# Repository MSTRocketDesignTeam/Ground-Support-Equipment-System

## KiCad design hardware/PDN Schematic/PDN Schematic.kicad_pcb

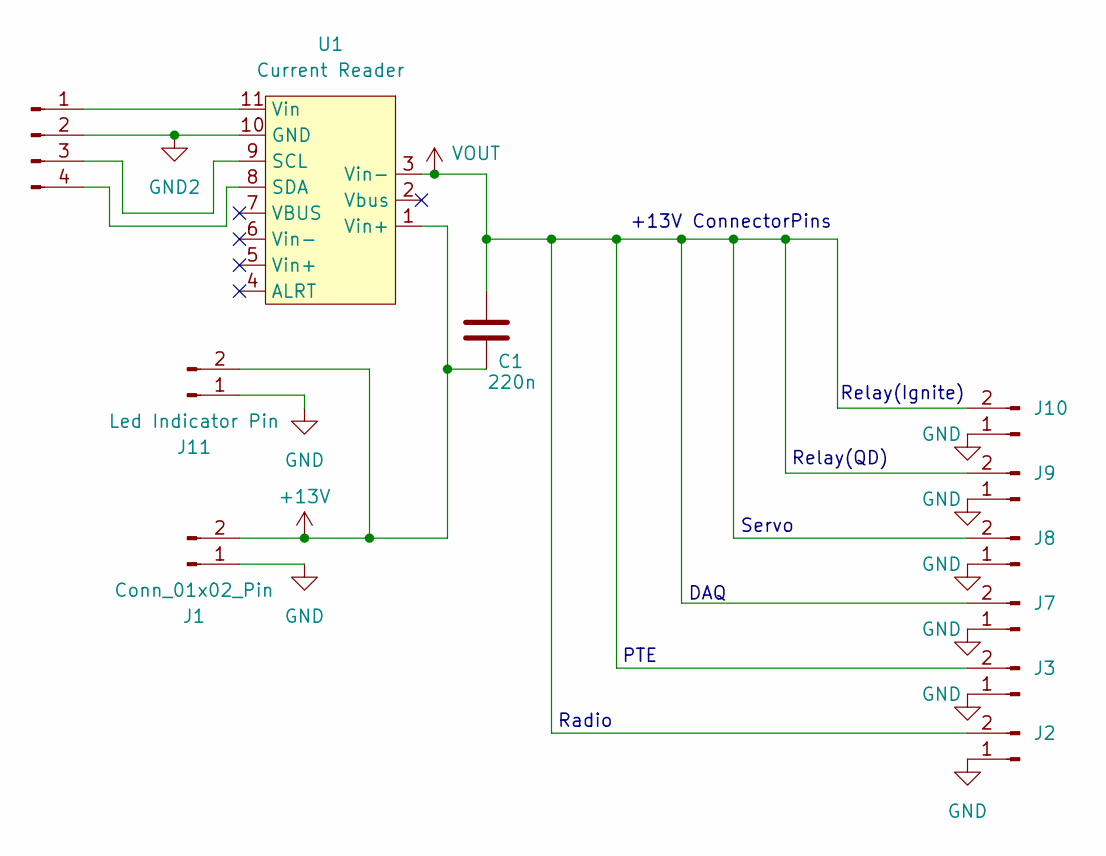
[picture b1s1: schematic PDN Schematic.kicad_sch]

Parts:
C1: 220n; C_0805_2012Metric; DigiKey Digikey: https://www.digikey.com/en/pro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
J1: Conn_01x02_Pin; AMASS_XT60-M_1x02_P7.20mm_Vertical
J2, J3, J7, J8, J9, J10: Conn_01x02_Pin; AMASS_XT30U-M_1x02_P5.0mm_Vertical
J4: Conn_01x04_Pin; PinHeader_1x04_P2.54mm_Vertical
J11: Led Indicator Pin; AMASS_XT30U-M_1x02_P5.0mm_Vertical
U1: Current Reader; INA238_MODULE

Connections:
+13V: C1.2, J1.2, J11.2, U1.1 (Vin+)
GND: J1.1, J2.1, J3.1, J7.1, J8.1, J9.1, J10.1, J11.1
GND2: J4.2, U1.10 (GND)
unnamed: J4.1, U1.11 (Vin)
unnamed: J4.3, U1.9 (SCL)
unnamed: J4.4, U1.8 (SDA)
VOUT: C1.1, J2.2, J3.2, J7.2, J8.2, J9.2, J10.2, U1.3 (Vin-)

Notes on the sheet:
Relay(Ignite)
Servo
Radio
Relay(QD)
+13V ConnectorPins
DAQ
PTE

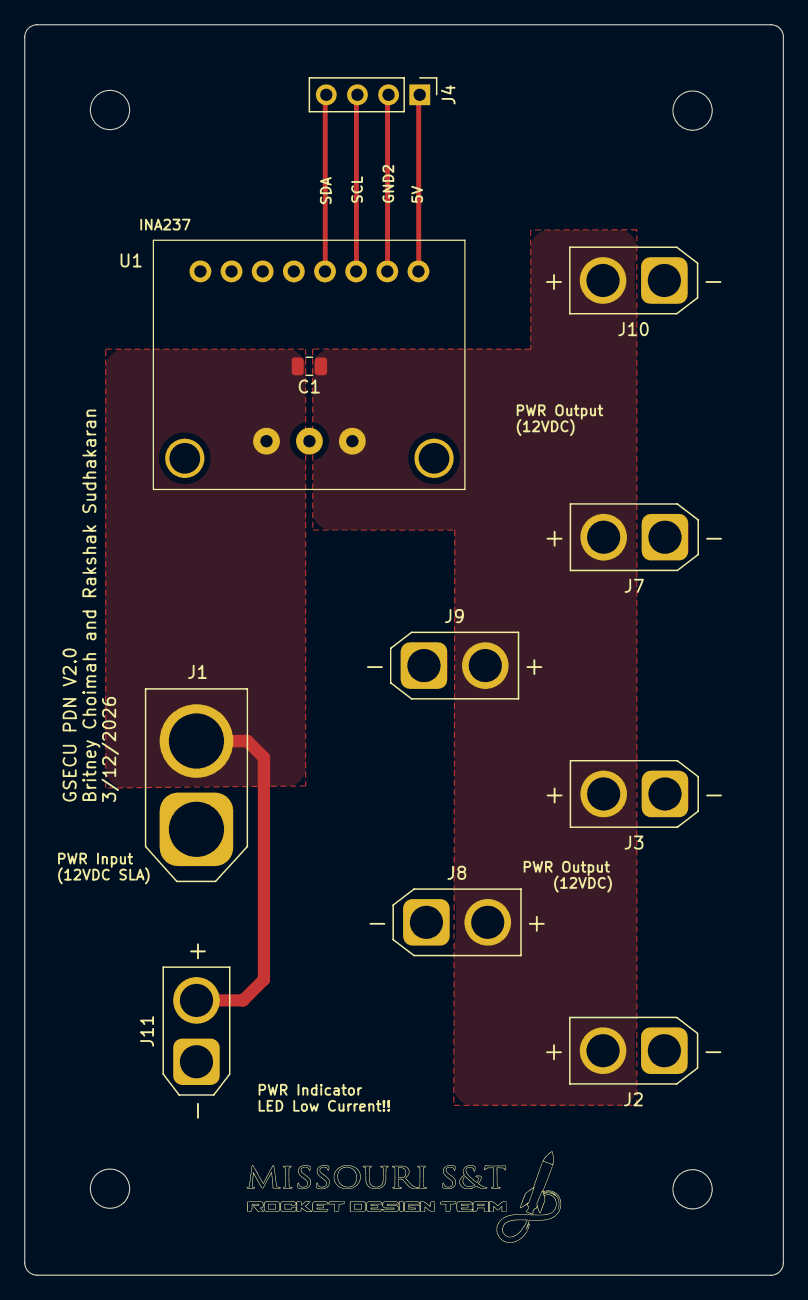
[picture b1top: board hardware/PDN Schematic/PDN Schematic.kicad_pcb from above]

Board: 2 copper layers, 61.9 x 102.0 mm, 11 parts (0 on the bottom side), 7 nets.

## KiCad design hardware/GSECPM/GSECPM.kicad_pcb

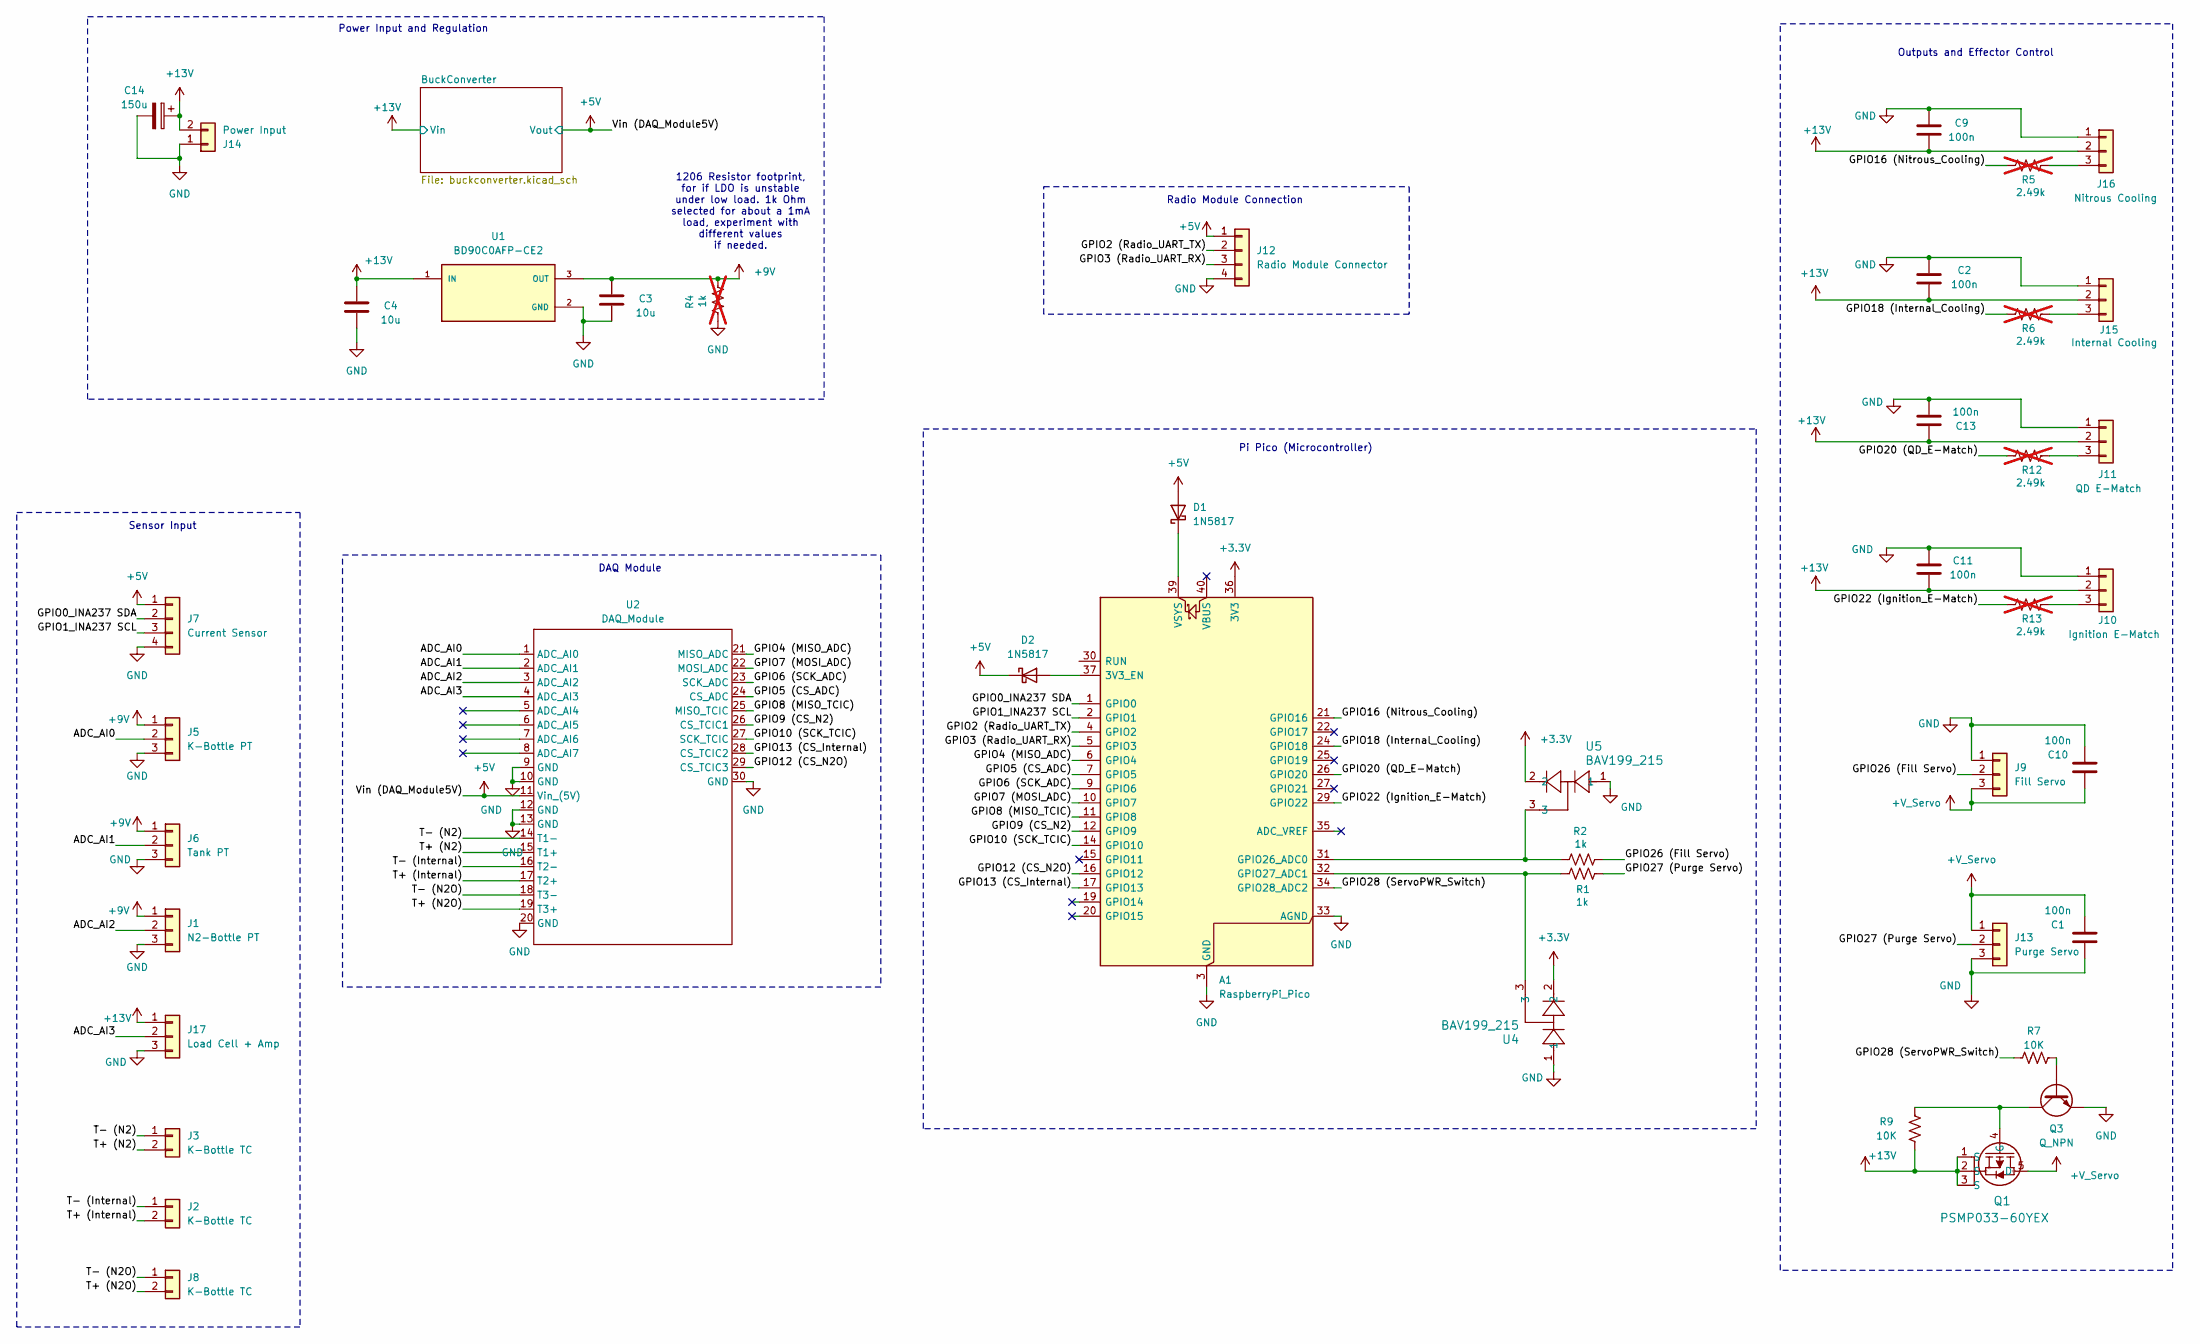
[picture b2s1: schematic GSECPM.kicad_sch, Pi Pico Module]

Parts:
A1: RaspberryPi_Pico; RaspberryPi_Pico_Common_Unspecified
C1, C2, C9, C10, C11, C13: 100n; C_0603_1608Metric
C3, C4: 10u; C_1210_3225Metric
C14: 150u; CAPPRD500W60D1000H1600
D1, D2: 1N5817; D_DO-41_SOD81_P10.16mm_Horizontal
J1: N2-Bottle PT; TerminalBlock_Xinya_XY308-2.54-3P_1x03_P2.54mm_Horizontal
J2, J3, J8: K-Bottle TC; TerminalBlock_Xinya_XY308-2.54-2P_1x02_P2.54mm_Horizontal
J5: K-Bottle PT; TerminalBlock_Xinya_XY308-2.54-3P_1x03_P2.54mm_Horizontal
J6: Tank PT; TerminalBlock_Xinya_XY308-2.54-3P_1x03_P2.54mm_Horizontal
J7: Current Sensor; PinHeader_1x04_P2.54mm_Vertical
J9: Fill Servo; TerminalBlock_Xinya_XY308-2.54-3P_1x03_P2.54mm_Horizontal
J10: Ignition E-Match; PinHeader_1x03_P2.54mm_Vertical
J11: QD E-Match; PinHeader_1x03_P2.54mm_Vertical
J12: Radio Module Connector; PinHeader_1x04_P2.54mm_Vertical
J13: Purge Servo; TerminalBlock_Xinya_XY308-2.54-3P_1x03_P2.54mm_Horizontal
J14: Power Input; AMASS_XT30U-M_1x02_P5.0mm_Vertical
J15: Internal Cooling; PinHeader_1x03_P2.54mm_Vertical
J16: Nitrous Cooling; PinHeader_1x03_P2.54mm_Vertical
J17: Load Cell + Amp; TerminalBlock_Xinya_XY308-2.54-3P_1x03_P2.54mm_Horizontal
Q1: PSMP033-60YEX; LFPAK_SOT669_NEX
Q3: Q_NPN; SOT-323_SC-70
R1, R2: 1k; R_0603_1608Metric
R4: 1k; R_1206_3216Metric; not fitted
R5, R6, R12, R13: 2.49k; R_0603_1608Metric; not fitted
R7, R9: 10K; R_0603_1608Metric
U1: BD90C0AFP-CE2; TO-252-2; PARTREV 23
U2: DAQ_Module
U4, U5: BAV199_215; TO-236AB_NEX

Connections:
+3.3V: A1.36 (3V3), U4.2, U5.2
+5V: D1.2 (A), D2.1 (K), J7.1, J12.1, U2.11 (Vin_(5V)); also elsewhere on the board
+9V: C3.2, J1.1, J5.1, J6.1, R4.1, U1.3 (OUT)
+13V: C2.1, C4.2, C9.1, C11.1, C13.1, C14.1, J10.2, J11.2, J14.2, J15.2, J16.2, J17.1, Q1.1 (S), Q1.2 (S), Q1.3 (S), R9.1, U1.1 (IN); also elsewhere on the board
+V_Servo: C1.2, C10.1, J9.3, J13.1, Q1.5 (D)
/ADC_AI0: J5.2, U2.1 (ADC_AI0)
/ADC_AI1: J6.2, U2.2 (ADC_AI1)
/ADC_AI2: J1.2, U2.3 (ADC_AI2)
/ADC_AI3: J17.2, U2.4 (ADC_AI3)
/GPIO0_INA237 SDA: A1.1 (GPIO0), J7.2
/GPIO1_INA237 SCL: A1.2 (GPIO1), J7.3
/GPIO2 (Radio_UART_TX): A1.4 (GPIO2), J12.2
/GPIO3 (Radio_UART_RX): A1.5 (GPIO3), J12.3
/GPIO4 (MISO_ADC): A1.6 (GPIO4), U2.21 (MISO_ADC)
/GPIO5 (CS_ADC): A1.7 (GPIO5), U2.24 (CS_ADC)
/GPIO6 (SCK_ADC): A1.9 (GPIO6), U2.23 (SCK_ADC)
/GPIO7 (MOSI_ADC): A1.10 (GPIO7), U2.22 (MOSI_ADC)
/GPIO8 (MISO_TCIC): A1.11 (GPIO8), U2.25 (MISO_TCIC)
/GPIO9 (CS_N2): A1.12 (GPIO9), U2.26 (CS_TCIC1)
/GPIO10 (SCK_TCIC): A1.14 (GPIO10), U2.27 (SCK_TCIC)
/GPIO12 (CS_N2O): A1.16 (GPIO12), U2.29 (CS_TCIC3)
/GPIO13 (CS_Internal): A1.17 (GPIO13), U2.28 (CS_TCIC2)
/GPIO16 (Nitrous_Cooling): A1.21 (GPIO16), R5.1
/GPIO18 (Internal_Cooling): A1.24 (GPIO18), R6.1
/GPIO20 (QD_E-Match): A1.26 (GPIO20), R12.1
/GPIO22 (Ignition_E-Match): A1.29 (GPIO22), R13.1
/GPIO26 (Fill Servo): J9.2, R2.1
/GPIO27 (Purge Servo): J13.2, R1.1
/GPIO28 (ServoPWR_Switch): A1.34 (GPIO28_ADC2), R7.2
/T+ (Internal): J2.2, U2.17 (T2+)
/T+ (N2): J3.2, U2.15 (T1+)
/T+ (N2O): J8.2, U2.19 (T3+)
/T- (Internal): J2.1, U2.16 (T2-)
/T- (N2): J3.1, U2.14 (T1-)
/T- (N2O): J8.1, U2.18 (T3-)
GND: A1.3 (GND), A1.8 (GND), A1.13 (GND), A1.18 (GND), A1.23 (GND), A1.28 (GND), A1.33 (AGND), A1.38 (GND), C1.1, C2.2, C3.1, C4.1, C9.2, C10.2, C11.2, C13.2, C14.2, J1.3, J5.3, J6.3, J7.4, J9.1, J10.1, J11.1, J12.4, J13.3, J14.1, J15.1, J16.1, J17.3, Q3.2 (E), R4.2, U1.2 (GND), U2.9 (GND), U2.10 (GND), U2.12 (GND), U2.13 (GND), U2.20 (GND), U2.30 (GND), U4.1, U5.1; also elsewhere on the board
unnamed: A1.37 (3V3_EN), D2.2 (A)
unnamed: A1.31 (GPIO26_ADC0), R2.2, U5.3
unnamed: A1.32 (GPIO27_ADC1), R1.2, U4.3
unnamed: A1.39 (VSYS), D1.1 (K)
unnamed: J10.3, R13.2
unnamed: J11.3, R12.2
unnamed: J15.3, R6.2
unnamed: J16.3, R5.2
unnamed: Q1.4 (G), Q3.3 (C), R9.2
unnamed: Q3.1 (B), R7.1

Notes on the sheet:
1206 Resistor footprint, for if LDO is unstable under low load. 1k Ohm selected for about a 1mA load, experiment with different values if needed.
Power Input and Regulation
Pi Pico (Microcontroller)
Sensor Input
DAQ Module
Outputs and Effector Control
Radio Module Connection

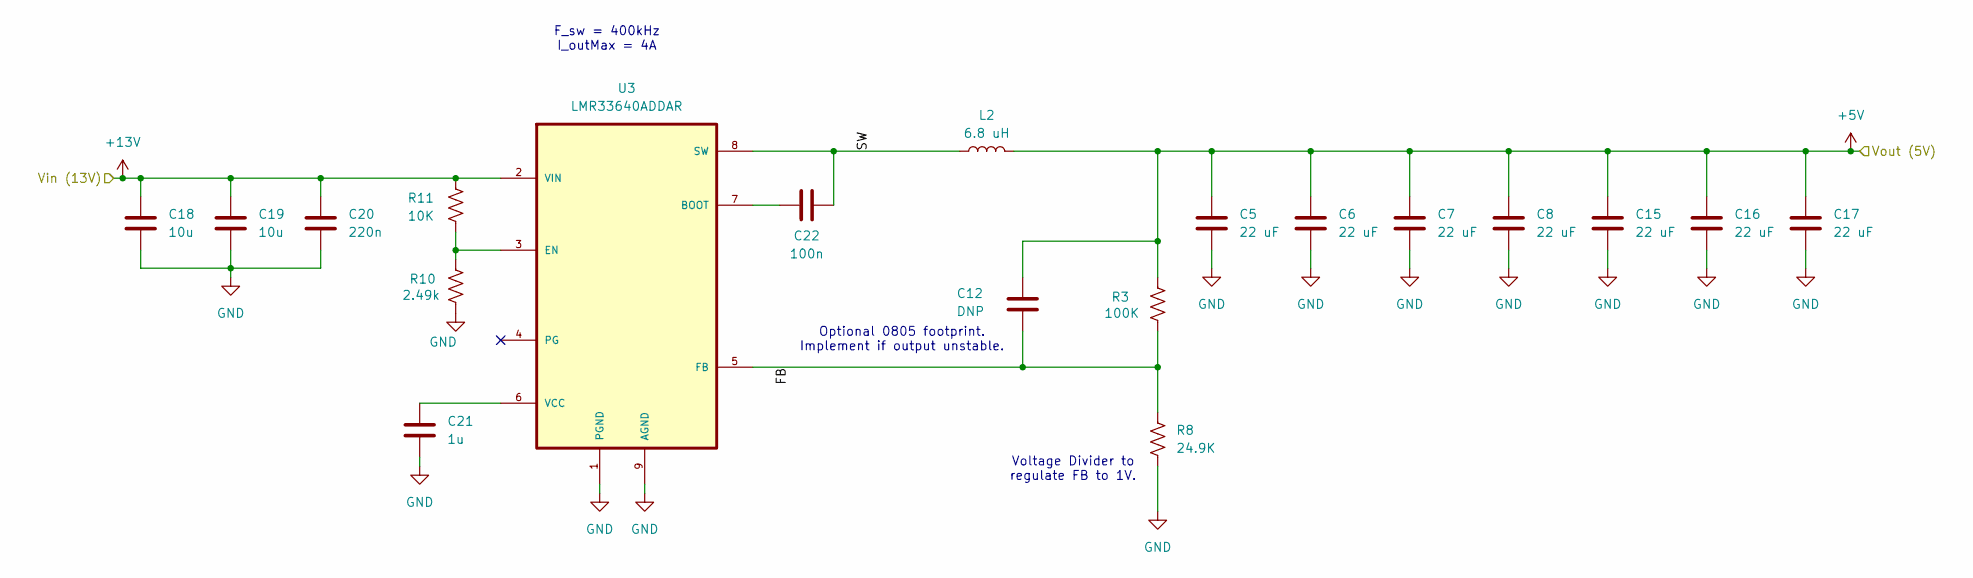
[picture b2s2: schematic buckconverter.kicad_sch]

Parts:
C5, C6, C7, C8, C15, C16, C17: 22 uF; C_0805_2012Metric
C12: DNP; C_0805_2012Metric
C18, C19: 10u; C_1210_3225Metric
C20: 220n; C_0805_2012Metric
C21: 1u; C_0805_2012Metric
C22: 100n; C_0603_1608Metric
L2: 6.8 uH; IND_CSBX0650-6R8M
R3: 100K; R_0603_1608Metric
R8: 24.9K; R_0603_1608Metric
R10: 2.49k; R_0603_1608Metric
R11: 10K; R_0603_1608Metric
U3: LMR33640ADDAR; Texas_HSOP-8-1EP_3.9x4.9mm_P1.27mm_ThermalVias

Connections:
+5V: C5.1, C6.1, C7.1, C8.1, C12.2, C15.1, C16.1, C17.1, L2.2, R3.2; also elsewhere on the board
+13V: C18.1, C19.1, C20.1, R11.1, U3.2 (VIN); also elsewhere on the board
/BuckConverter/FB: C12.1, R3.1, R8.1, U3.5 (FB)
/BuckConverter/SW: C22.2, L2.1, U3.8 (SW)
GND: C5.2, C6.2, C7.2, C8.2, C15.2, C16.2, C17.2, C18.2, C19.2, C20.2, C21.2, R8.2, R10.1, U3.1 (PGND), U3.9 (AGND); also elsewhere on the board
unnamed: C22.1, U3.7 (BOOT)
unnamed: R10.2, R11.2, U3.3 (EN)
unnamed: C21.1, U3.6 (VCC)

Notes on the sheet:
Optional 0805 footprint. Implement if output unstable.
Voltage Divider to regulate FB to 1V.
F_sw = 400kHz I_outMax = 4A

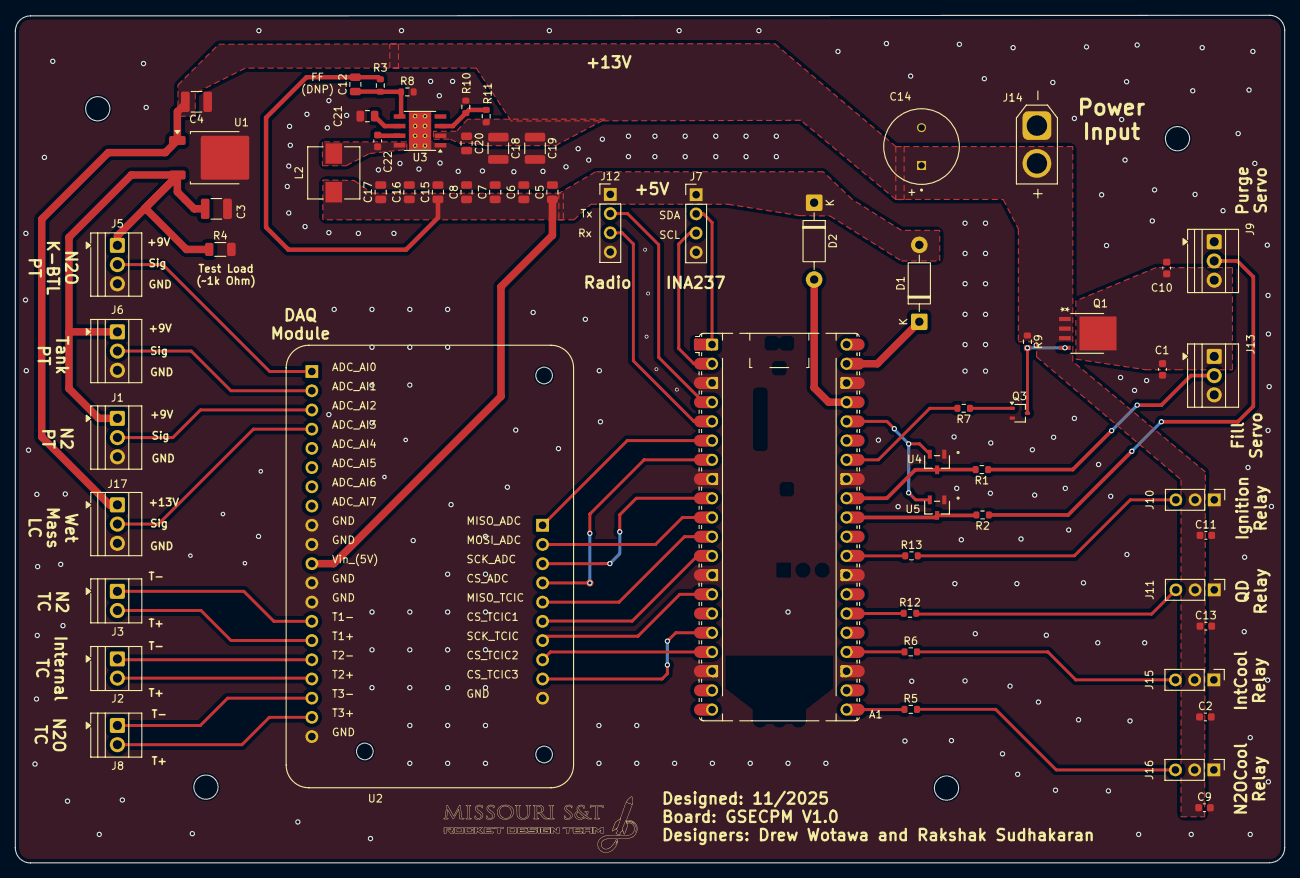
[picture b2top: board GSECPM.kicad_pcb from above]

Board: 2 copper layers, 167.8 x 112.0 mm, 62 parts (0 on the bottom side), 51 nets.

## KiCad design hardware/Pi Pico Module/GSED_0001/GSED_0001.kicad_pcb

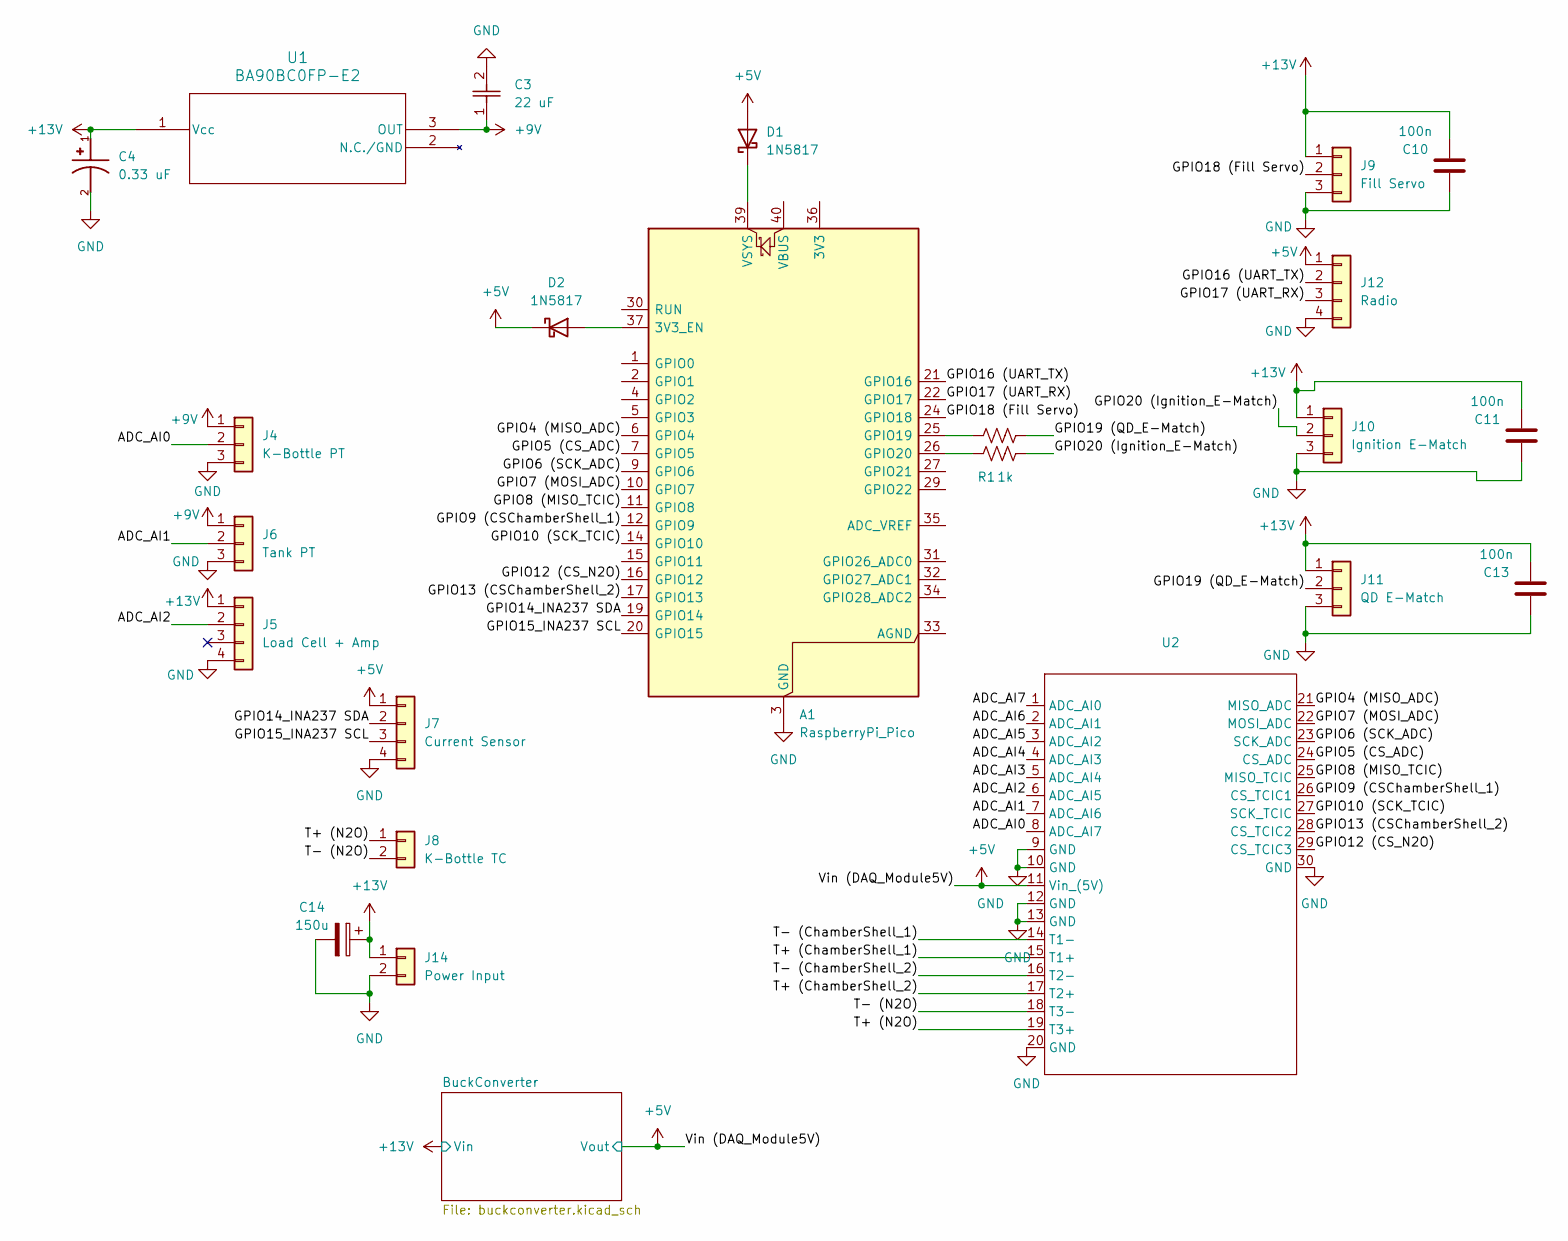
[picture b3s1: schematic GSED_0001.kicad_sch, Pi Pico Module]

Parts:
A1: RaspberryPi_Pico; RaspberryPi_Pico_Common_Unspecified
C3: 22 uF; C_0805_2012Metric
C4: 0.33 uF; CAPMP3216X180N; PARTREV 031320
C10, C11, C13: 100n; C_0603_1608Metric
C14: 150u; CAPPRD500W60D1000H1600
D1, D2: 1N5817; D_DO-41_SOD81_P10.16mm_Horizontal
J4: K-Bottle PT; PinHeader_1x03_P2.54mm_Vertical
J5: Load Cell + Amp; PinHeader_1x04_P2.54mm_Vertical
J6: Tank PT; PinHeader_1x03_P2.54mm_Vertical
J7: Current Sensor; PinHeader_1x04_P2.54mm_Vertical
J8: K-Bottle TC; AMKPCB
J9: Fill Servo; PinHeader_1x03_P2.54mm_Vertical
J10: Ignition E-Match; PinHeader_1x03_P2.54mm_Vertical
J11: QD E-Match; PinHeader_1x03_P2.54mm_Vertical
J12: Radio; PinHeader_1x04_P2.54mm_Vertical
J14: Power Input; AMASS_XT30U-M_1x02_P5.0mm_Vertical
R1, R2: 1k; R_0603_1608Metric
U1: BA90BC0FP-E2; TO252-3_ROM
U2: DAQ_Module

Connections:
+5V: D1.2 (A), D2.1 (K), J7.1, J12.1, U2.11 (Vin_(5V)); also elsewhere on the board
+9V: C3.1, J4.1, J6.1, U1.3 (OUT)
+13V: C4.1, C10.2, C11.2, C13.2, C14.1, J5.1, J9.1, J10.1, J11.1, J14.1, U1.1 (Vcc); also elsewhere on the board
/ADC_AI0: J4.2, U2.8 (ADC_AI7)
/ADC_AI1: J6.2, U2.7 (ADC_AI6)
/ADC_AI2: J5.2, U2.6 (ADC_AI5)
/ADC_AI3: U2.5 (ADC_AI4)
/ADC_AI4: U2.4 (ADC_AI3)
/ADC_AI5: U2.3 (ADC_AI2)
/ADC_AI6: U2.2 (ADC_AI1)
/ADC_AI7: U2.1 (ADC_AI0)
/GPIO4 (MISO_ADC): A1.6 (GPIO4), U2.21 (MISO_ADC)
/GPIO5 (CS_ADC): A1.7 (GPIO5), U2.24 (CS_ADC)
/GPIO6 (SCK_ADC): A1.9 (GPIO6), U2.23 (SCK_ADC)
/GPIO7 (MOSI_ADC): A1.10 (GPIO7), U2.22 (MOSI_ADC)
/GPIO8 (MISO_TCIC): A1.11 (GPIO8), U2.25 (MISO_TCIC)
/GPIO9 (CSChamberShell_1): A1.12 (GPIO9), U2.26 (CS_TCIC1)
/GPIO10 (SCK_TCIC): A1.14 (GPIO10), U2.27 (SCK_TCIC)
/GPIO12 (CS_N2O): A1.16 (GPIO12), U2.29 (CS_TCIC3)
/GPIO13 (CSChamberShell_2): A1.17 (GPIO13), U2.28 (CS_TCIC2)
/GPIO14_INA237 SDA: A1.19 (GPIO14), J7.2
/GPIO15_INA237 SCL: A1.20 (GPIO15), J7.3
/GPIO16 (UART_TX): A1.21 (GPIO16), J12.2
/GPIO17 (UART_RX): A1.22 (GPIO17), J12.3
/GPIO18 (Fill Servo): A1.24 (GPIO18), J9.2
/GPIO19 (QD_E-Match): J11.2, R2.1
/GPIO20 (Ignition_E-Match): J10.2, R1.1
/T+ (ChamberShell_1): U2.15 (T1+)
/T+ (ChamberShell_2): U2.17 (T2+)
/T+ (N2O): J8.1, U2.19 (T3+)
/T- (ChamberShell_1): U2.14 (T1-)
/T- (ChamberShell_2): U2.16 (T2-)
/T- (N2O): J8.2, U2.18 (T3-)
GND: A1.3 (GND), A1.8 (GND), A1.13 (GND), A1.18 (GND), A1.23 (GND), A1.28 (GND), A1.38 (GND), C3.2, C4.2, C10.1, C11.1, C13.1, C14.2, J4.3, J5.4, J6.3, J7.4, J9.3, J10.3, J11.3, J12.4, J14.2, U2.9 (GND), U2.10 (GND), U2.12 (GND), U2.13 (GND), U2.20 (GND), U2.30 (GND); also elsewhere on the board
unnamed: A1.37 (3V3_EN), D2.2 (A)
unnamed: A1.25 (GPIO19), R2.2
unnamed: A1.26 (GPIO20), R1.2
unnamed: A1.39 (VSYS), D1.1 (K)

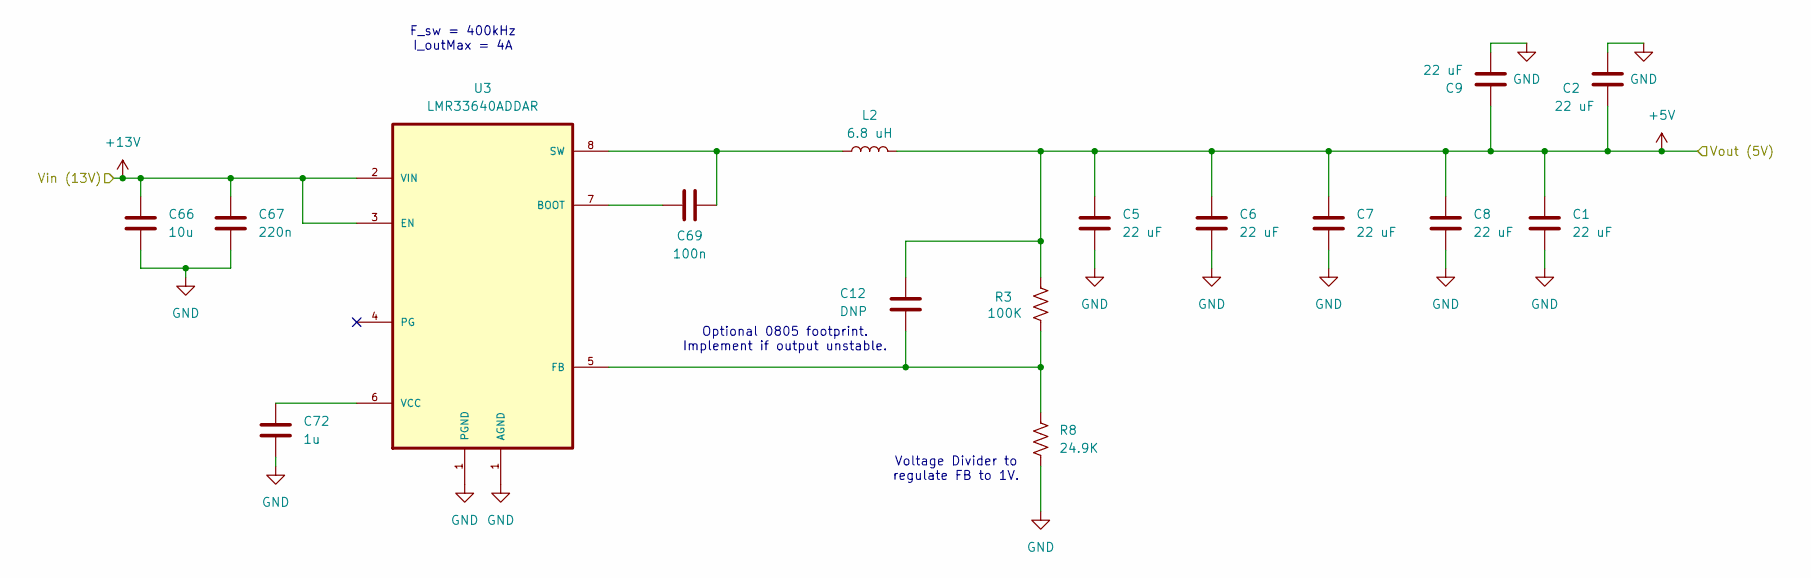
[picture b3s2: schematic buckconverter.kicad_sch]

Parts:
C1, C2, C5, C6, C7, C8, C9: 22 uF; C_0805_2012Metric
C12: DNP; C_0805_2012Metric
C66: 10u; C_0805_2012Metric
C67: 220n; C_0805_2012Metric
C69: 100n; C_0603_1608Metric
C72: 1u; C_0805_2012Metric
L2: 6.8 uH; IND_CSBX0650-6R8M
R3: 100K; R_0603_1608Metric
R8: 24.9K; R_0603_1608Metric
U3: LMR33640ADDAR; Texas_HSOP-8-1EP_3.9x4.9mm_P1.27mm_ThermalVias

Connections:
+5V: C1.1, C2.1, C5.1, C6.1, C7.1, C8.1, C9.1, C12.2, L2.2, R3.2; also elsewhere on the board
+13V: C66.1, C67.1, U3.2 (VIN), U3.3 (EN); also elsewhere on the board
GND: C1.2, C2.2, C5.2, C6.2, C7.2, C8.2, C9.2, C66.2, C67.2, C72.2, R8.2, U3.1 (PGND); also elsewhere on the board
unnamed: C69.1, U3.7 (BOOT)
unnamed: C12.1, R3.1, R8.1, U3.5 (FB)
unnamed: C69.2, L2.1, U3.8 (SW)
unnamed: C72.1, U3.6 (VCC)

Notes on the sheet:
Optional 0805 footprint. Implement if output unstable.
Voltage Divider to regulate FB to 1V.
F_sw = 400kHz I_outMax = 4A

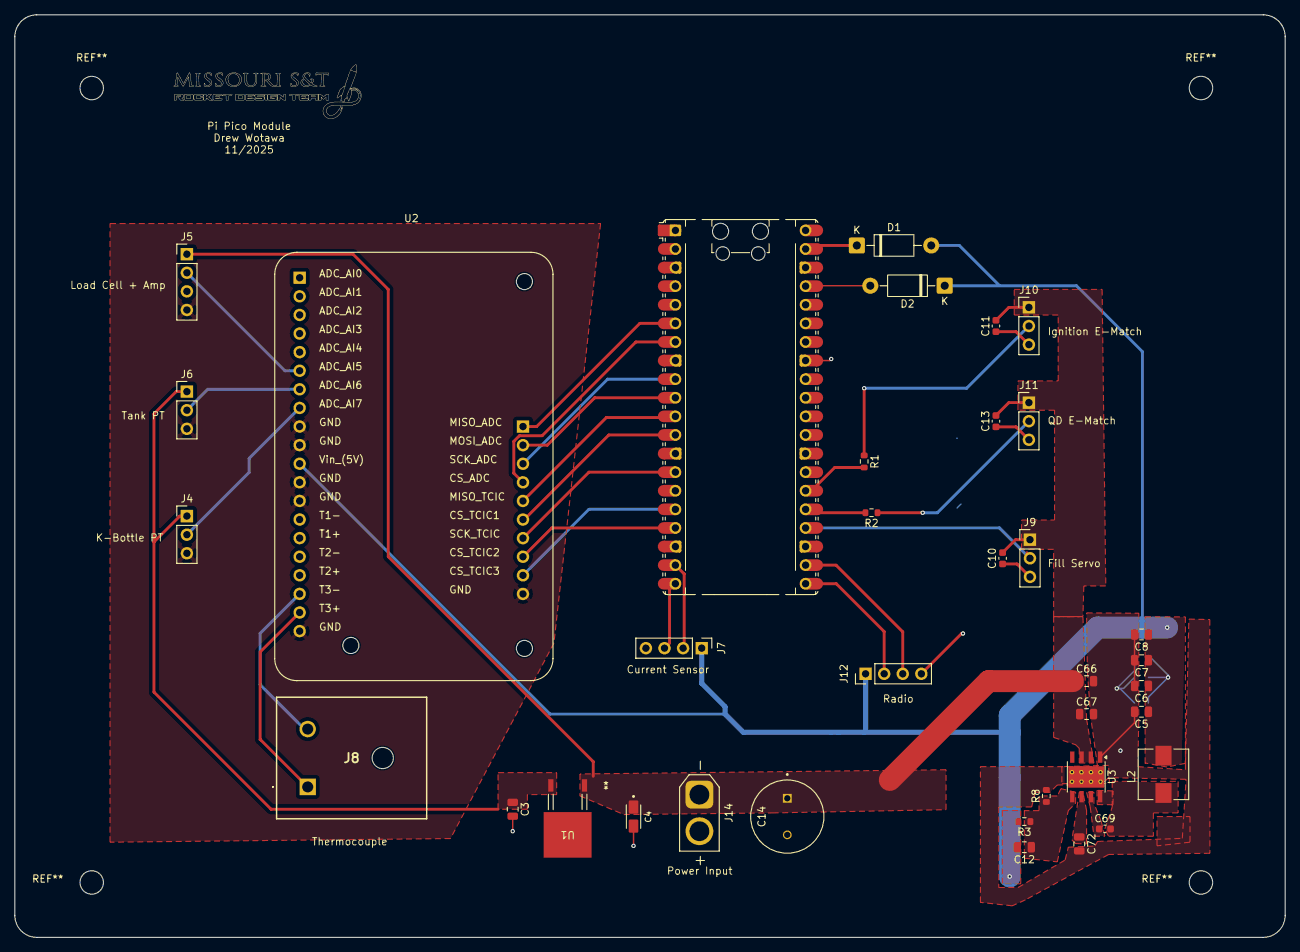
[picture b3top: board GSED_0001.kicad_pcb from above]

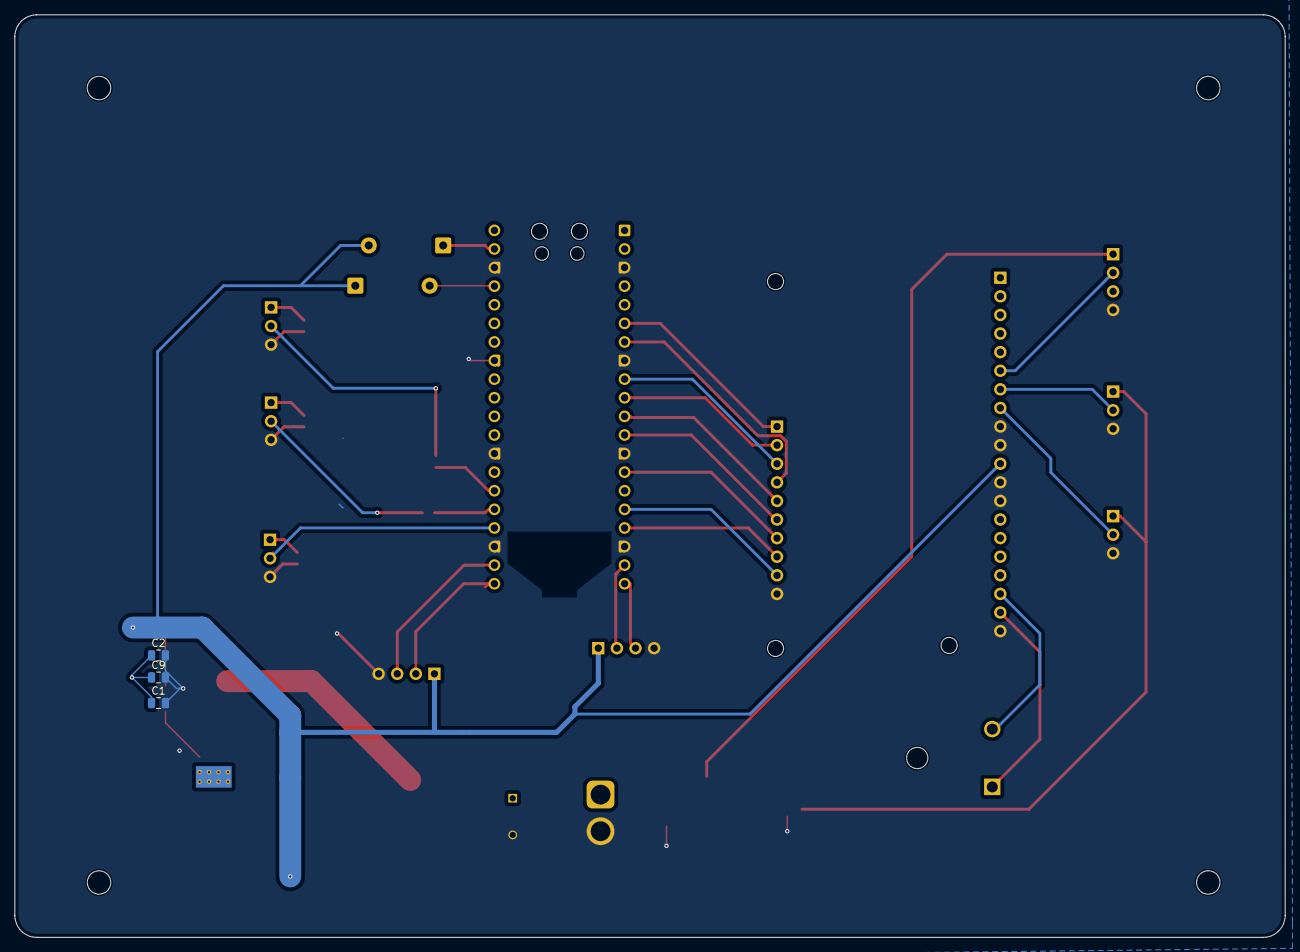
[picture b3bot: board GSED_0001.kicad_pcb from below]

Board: 2 copper layers, 173.5 x 126.0 mm, 39 parts (3 on the bottom side), 33 nets.

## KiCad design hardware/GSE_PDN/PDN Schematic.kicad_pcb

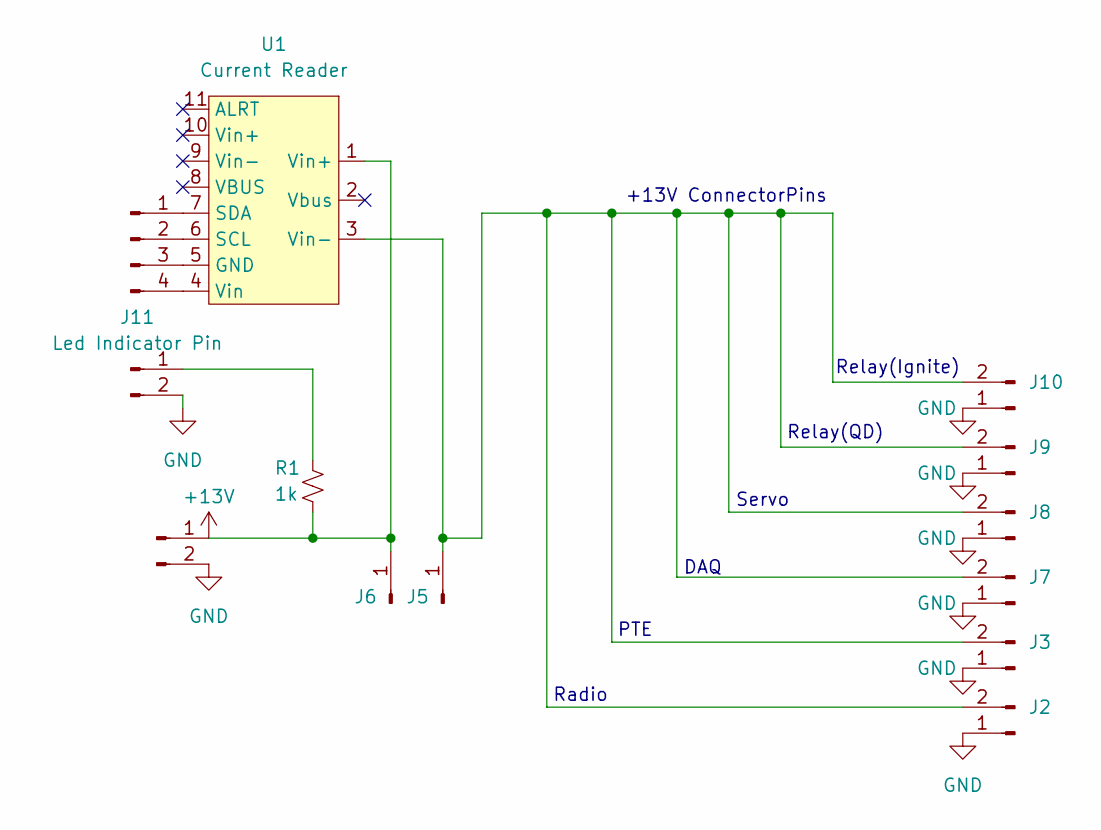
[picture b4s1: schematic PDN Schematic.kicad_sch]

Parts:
J1, J2, J3, J7, J8, J9, J10: Conn_01x02_Pin; PinHeader_1x02_P2.54mm_Vertical
J4: Conn_01x04_Pin; PinHeader_1x04_P2.54mm_Vertical
J5, J6: Conn_01x01_Pin; PinHeader_1x01_P2.54mm_Vertical
J11: Led Indicator Pin; PinHeader_1x02_P2.54mm_Vertical
R1: 1k; R_1206_3216Metric
U1: Current Reader; INA238_MODULE

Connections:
+13V: J1.1, J6.1, R1.2, U1.1 (Vin+)
GND: J1.2, J2.1, J3.1, J7.1, J8.1, J9.1, J10.1, J11.2
unnamed: J4.1, U1.7 (SDA)
unnamed: J4.2, U1.6 (SCL)
unnamed: J4.3, U1.5 (GND)
unnamed: J4.4, U1.4 (Vin)
unnamed: J2.2, J3.2, J5.1, J7.2, J8.2, J9.2, J10.2, U1.3 (Vin-)
unnamed: J11.1, R1.1

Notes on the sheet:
Relay(Ignite)
Servo
Radio
Relay(QD)
+13V ConnectorPins
DAQ
PTE

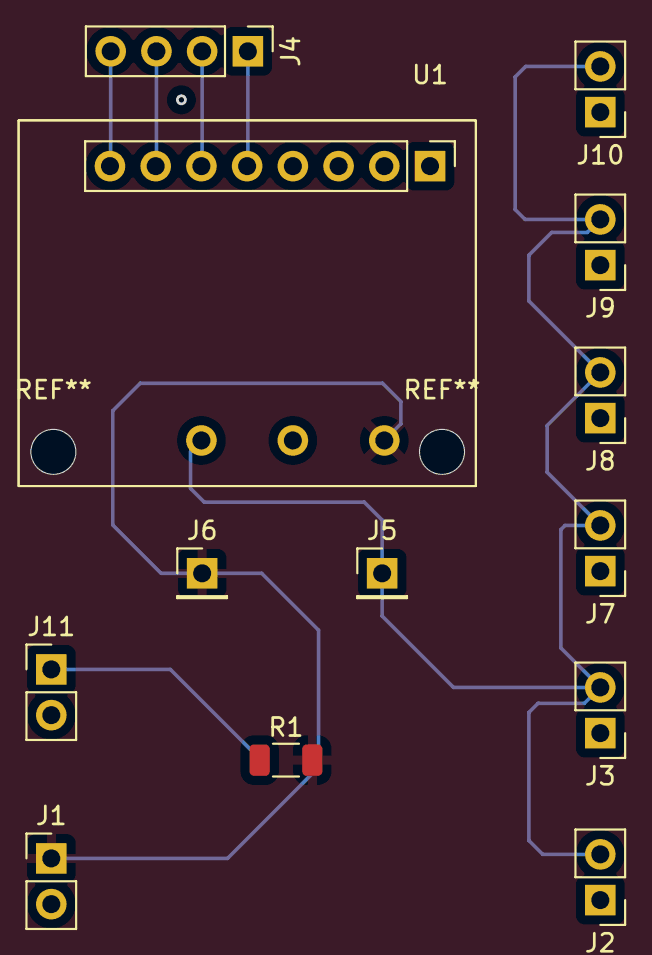
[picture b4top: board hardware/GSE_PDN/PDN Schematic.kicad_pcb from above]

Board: 2 copper layers, 13 parts (0 on the bottom side), 8 nets.

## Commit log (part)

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2025-02-08 Rakshak Sudhakaran - GUI appearance meets functional requirements for launch
2025-02-08 Updated GSECPicoSW with changes made to cold flow pico sw regarding constant usage
2025-02-12 Rakshak Sudhakaran - Added some more hardware functionality. Need to update pico SW to be compatible with it. Need to find a way to implement hardware functionality with custom toggle and/or rework c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
2025-02-16 Updates to coldFlowTest, need to update positioning of GUI elements in accordance with proper functional HMI design
2025-02-17 Rakshak Sudhakaran - Updated cold flow SW to allow control for 2 servos and user input run time
2025-02-17 Updated GSEC Pico Cold Flow SW for operation of two servos
2025-03-06 Updated control angle definition of the servos
2025-03-06 Updated servo control angle definitions
2025-09-26 GSE PDN Files
2025-10-03 Close to finalized PCB Layout for GSE PDN
2025-10-04 V1 of schematic
2025-10-17 Hopefully finished schematic
2025-10-17 Imported footprints and libraries
2025-10-17 almost finalized GSE PDN files
2025-10-18 Added footprints and things
2025-10-18 Reuploaded folder
2025-10-19 Extra GSE PDN Board changes
2025-10-24 proper library pathing
2025-10-30 Updated PCB
2025-10-31 Finalish PDN Board
2025-10-31 Hopefully finished PCB
2025-11-06 Generated build files and added component data
2025-11-07 Finished Board
2025-11-14 switched GUI to ttk
2025-11-14 misc commit
2025-11-14 Done
2025-11-14 Ready for final review
2025-11-14 Moved some silkscreen text around
2025-11-15 Swapped positions of radio and INA237 conns for optimized current loop. Swapped 9V LDO to a TI model that supports newer ceramic caps better than the original STM legacy LDO
2025-11-15 resolved single click working on toggles
2025-11-17 Made all buck components on front layer
2025-11-18 Better buck converter positioning with inductor further from analog signals. Improved via stitching and fixed split ground planes somewhat except for Manhattans
2026-01-25 Finished PCBs with production files
2026-03-05 Removed redudancies
2026-03-05 Revert "Rakshak Sudhakaran - Forgot to say that I made the previous commit from SandTRocket regarding updated control logic"
    This reverts commit 2741b68b2c3f01766e19b41769328f6443dd0d30.
2026-03-07 Added windows support
2026-03-07 added stop button
2026-03-07 fixed bugs preventing valves from moving
2026-03-26 Intermediate commit. DAQ code works occasionally (best after 15 mins of power off period!?!?). I think something isn't being configured correctly with the ADC
2026-04-03 Some GUI changes, fixed some race conditions
2026-04-12 Added GSE operation timers and a terminal launch sequence status bar, as well as recursively updating GSECPico status indicators
2026-04-12 Pulled a draft version of SP26SWSandbox into main
2026-04-16 Post hotfire 1 baseline. Launch sequence timing is finalized. Ready to modify for DAQ stuff
2026-04-16 Fixed GUI frame/widget arrangment and made work for center monitor resizing
2026-04-16 Finally merged with SP26SWSandbox
2026-04-26 Made some msg parsing improvements for cold flow testing SW
2026-04-27 Added pico cold flow software to be used by the GSECU. No servo power switch functionality implemented yet
2026-04-30 Pre DAQ functionality implementation baseline
2026-05-09 DAQ functionality working!
2026-05-09 Implemented DAQ functionality on main, need to implement live plotting and accurate engineering value conversions
2026-05-10 Improved data file naming, added sensor calibration framework
2026-05-10 Updated launch sequence logic
2026-05-10 Intermediary commit for debugging serial latency issues
2026-05-13 Fixed latency issue on GSEC Pico SW, but broke LEC transmit :(
2026-05-13 Changed QD and N2O value buttons
2026-05-13 Fixed latency issue and fixed LEC transmit. GSE DAQ and hardware control work seamlessly. Need to implement LEC DAQ now
2026-05-13 LECU DAQ working, but extremely slowly and the readings are off because the bit shift operations are most likely incorrect
2026-05-14 Working LEC and GSE DAQ commit! No latency
2026-05-14 LEC and GSE DAQ working! No latency!
2026-05-18 Added scales for TCs
2026-05-19 Formatting updates. Ready for launch
